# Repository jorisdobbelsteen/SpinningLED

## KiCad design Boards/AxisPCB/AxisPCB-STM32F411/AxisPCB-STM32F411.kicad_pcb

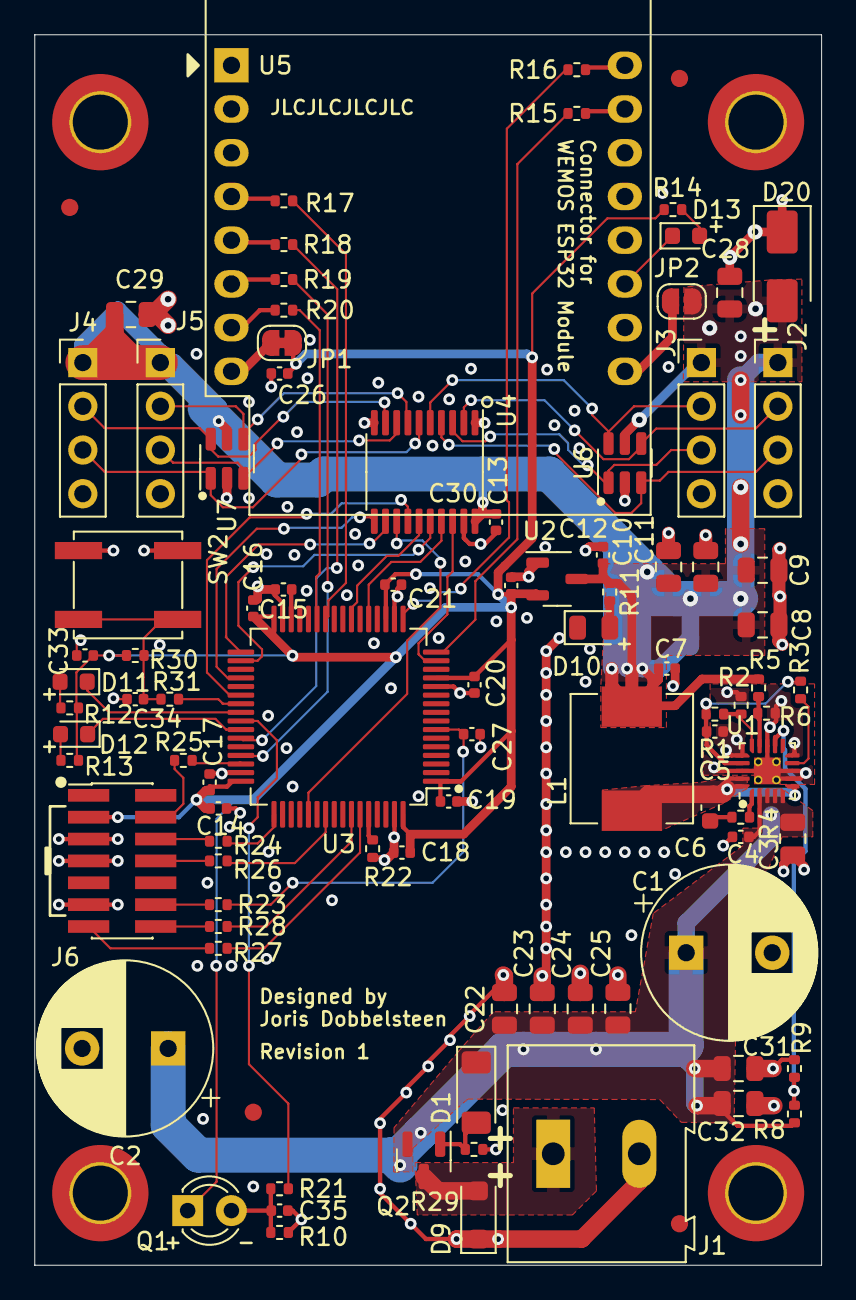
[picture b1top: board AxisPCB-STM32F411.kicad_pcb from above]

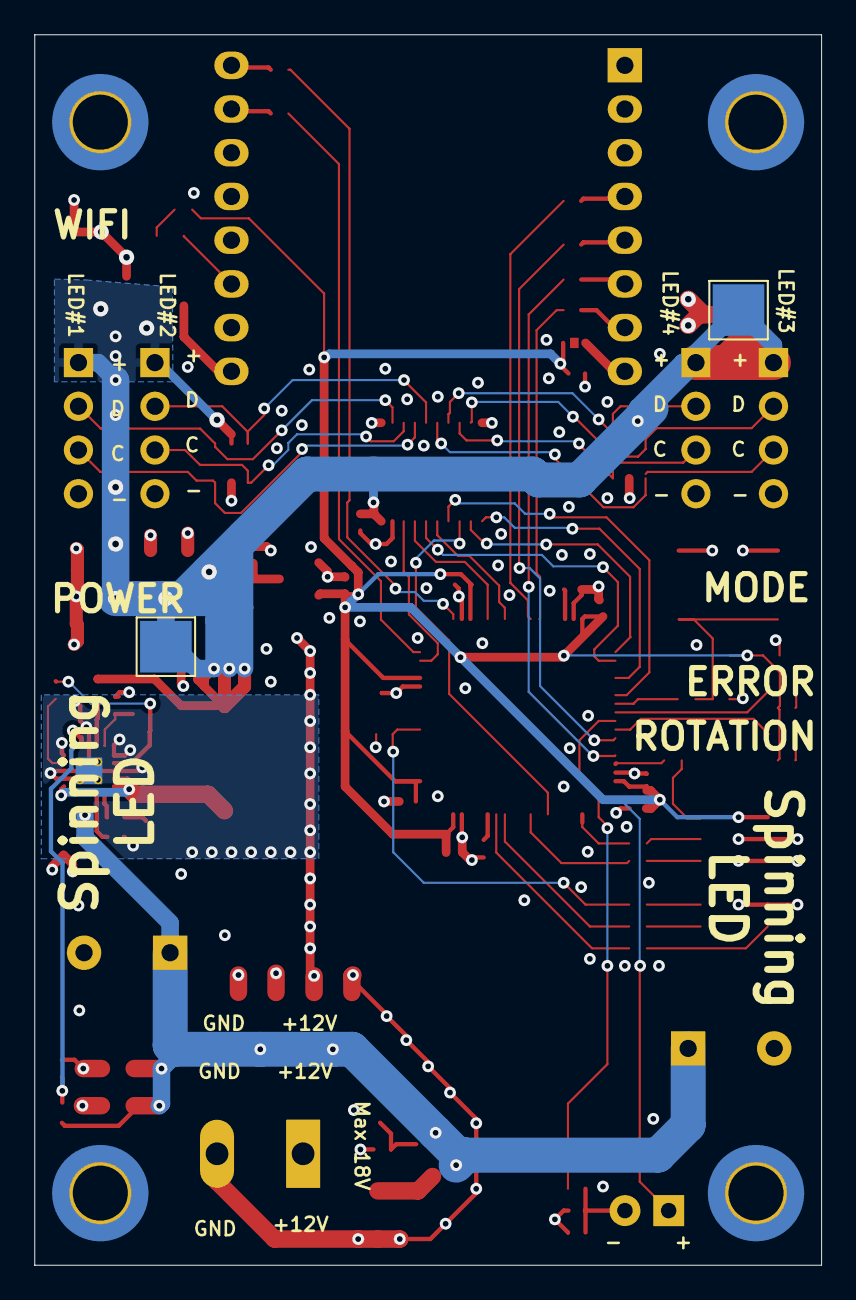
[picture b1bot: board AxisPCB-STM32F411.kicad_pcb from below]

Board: 4 copper layers, 45.7 x 71.5 mm, 101 parts (2 on the bottom side), 69 nets.

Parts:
C1, C2: 470u; CP_Radial_D10.0mm_P5.00mm
C3, C22, C23, C24, C25, C31, C32: 22u; C_0805_2012Metric
C4, C5, C12, C13, C33: 1u; C_0402_1005Metric
C6: 4u7; C_0603_1608Metric
C7, C16, C17, C18, C19, C20, C21, C27, C30, C34, C35: 0.1u; C_0402_1005Metric
C8, C9, C10, C11, C28, C29: 47u; C_0805_2012Metric
C14, C15, C26: 4.7u; C_0402_1005Metric
D1: ZMM5V6-M; D_MiniMELF
D9: SMF30CA; D_SOD-123F
D10: GREEN LED; LED_0805_2012Metric
D11: RED LED; LED_0603_1608Metric
D12: YELLOW LED; LED_0603_1608Metric
D13: BLUE LED; LED_0603_1608Metric
D20: SMAJ5.0A; D_SMA
FID1, FID2, FID3, FID4: Fiducial; Fiducial_1mm_Mask2mm
H1, H2, H3, H4: M3 Hole; MountingHole_3.2mm_M3_DIN965_Pad_TopBottom
J1: Conn_01x02_Pin; TerminalBlock_Altech_AK300-2_P5.00mm
J2, J3, J4, J5: Conn_01x04; PinHeader_1x04_P2.54mm_Vertical
J6: Conn_ST_STDC14; PinHeader_2x07_P1.27mm_Vertical_SMD
JP1: SolderJumper_2_Bridged; SolderJumper-2_P1.3mm_Bridged_RoundedPad1.0x1.5mm
JP2: SolderJumper_2_Open; SolderJumper-2_P1.3mm_Open_RoundedPad1.0x1.5mm
L1: 1.5u; L_Sunlord_MWSA0603S
Q1: INL-3APT30; LED_D3.0mm_Clear
Q2: AO3401A; SOT-23
R1: 330k 1%; R_0402_1005Metric
R2: 15k 1%; R_0402_1005Metric
R3: 100k; R_0402_1005Metric
R4: 0R; R_0402_1005Metric
R5: 200k 1%; R_0402_1005Metric
R6: 27k 1%; R_0402_1005Metric
R8: 200k; R_0402_1005Metric
R9: 51k; R_0402_1005Metric
R10, R29: 2K; R_0402_1005Metric
R11: 2.4k; R_0402_1005Metric
R12, R14, R31: 680R; R_0402_1005Metric
R13: 1.5k; R_0402_1005Metric
R15, R16, R17, R18, R19, R20, R23, R24, R25, R26: 22R; R_0402_1005Metric
R21, R27, R28: 100R; R_0402_1005Metric
R22, R30: 10k; R_0402_1005Metric
SW2: USER; SW_SPST_EVPBF
TP1, TP2: VCC; TestPoint_Pad_3.0x3.0mm
U1: TPS51396ARJER; VQFN-20-1EP_3x3mm_P0.45mm_EP1.55x1.55mm_ThermalVias
U2: XC6206P332MR; SOT-23-3
U3: STM32F411R_C-E_Tx; LQFP-64_10x10mm_P0.5mm
U4: 74AHCT245PW; TSSOP-20_4.4x6.5mm_P0.65mm
U5: WeMos_D1_mini; WEMOS_D1_mini_light
U6, U7: SRV05-4; SOT-23-6

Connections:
+3.3V: C13.1, C14.1, C16.2, C17.1, C18.1, C19.1, C20.1, C21.1, C26.1, C33.1, J6.3 (VCC), JP1.1 (A), Q1.1 (C), R12.1, R13.2, R14.2, R30.1, U2.2 (VO), U3.1 (VBAT), U3.13 (VDDA), U3.19 (VDD), U3.32 (VDD), U3.48 (VDD), U3.64 (VDD)
+5V: C7.1, C8.1, C9.1, C10.1, C11.1, C12.1, C28.1, C29.1, C30.1, D20.2 (A2), J2.1, J3.1, J4.1, J5.1, JP2.1 (A), L1.2, R5.1, R11.1, TP1.1, TP2.1, U2.3 (VI), U4.20 (VCC), U6.5 (VP), U7.5 (VP)
+12V: C1.1, C2.1, C3.1, C4.1, C22.1, C23.1, C24.1, C25.1, C31.1, C32.1, D1.1 (K), Q2.2 (S), R8.1, U1.2 (VIN), U1.3 (VIN_2), U1.4 (VIN_3), U1.5 (VIN_4)
/+12V_PIN: D9.2 (A2), J1.1, Q2.3 (D)
/SMPS 5V 8A/SW: C6.1, L1.1, U1.6 (SW), U1.19 (SW_2), U1.20 (SW_3)
/SMPS 5V 8A/VCC: C5.1, R1.1, R3.1, U1.17 (VCC)
BOOT0: R22.1, U3.60 (BOOT0)
ERROR_LED: D11.1 (K), U3.40 (PC9)
GND: C1.2, C2.2, C3.2, C4.2, C5.2, C7.2, C8.2, C9.2, C10.2, C11.2, C12.2, C13.2, C14.2, C15.2, C16.1, C17.2, C18.2, C19.2, C20.2, C21.2, C22.2, C23.2, C24.2, C25.2, C26.2, C27.2, C28.2, C29.2, C30.2, C31.2, C32.2, C33.2, C34.2, C35.1, D9.1 (A1), D10.1 (K), D20.1 (A1), H1.1, H2.1, H3.1, H4.1, J1.2, J2.4, J3.4, J4.4, J5.4, J6.5 (GND), J6.7 (GND), J6.11 (GNDDetect), R2.2, R6.2, R9.2, R10.2, R22.2, R29.2, SW2.1, U1.7 (GND), U1.8 (GND_2), U1.10 (NC_1), U1.13 (AGND), U1.16 (NC_2), U1.18 (GND_3), U1.21 (GND_4), U2.1 (GND), U3.12 (VSSA), U3.18 (VSS), U3.31 (VSS), U3.47 (VSS), U3.63 (VSS), U4.1 (A->B), U4.10 (GND), U4.19 (CE), U5.10 (GND), U6.2 (VN), U7.2 (VN)
LS1_C: J2.3, U4.4 (A2), U6.3 (IO2)
LS1_D: J2.2, U4.2 (A0), U6.4 (IO3)
LS2_C: J3.3, U4.3 (A1), U6.1 (IO1)
LS2_D: J3.2, U4.5 (A3), U6.6 (IO4)
LS3_C: J4.3, U4.6 (A4), U7.1 (IO1)
LS3_D: J4.2, U4.9 (A7), U7.6 (IO4)
LS4_C: J5.3, U4.8 (A6), U7.3 (IO2)
LS4_D: J5.2, U4.7 (A5), U7.4 (IO3)
NRST: C27.1, R23.1, U3.7 (NRST)
unnamed: C6.2, R4.2
unnamed: C34.1, R30.2, R31.2, SW2.2
unnamed: D1.2 (A), Q2.1 (G), R29.1
unnamed: D10.2 (A), R11.2
unnamed: D11.2 (A), R12.2
unnamed: D12.2 (A), R13.1
unnamed: D13.2 (A), R14.1
unnamed: J6.6 (JCLK/SWCLK), R24.2
unnamed: J6.8 (JTDO/SWO), R26.2
unnamed: J6.4 (JTMS/SWDIO), R25.2
unnamed: J6.13 (VCP_RX), R27.1
unnamed: J6.14 (VCP_TX), R28.1
unnamed: J6.12 (~RST), R23.2
unnamed: JP1.2 (B), U5.8 (3V3)
unnamed: JP2.2 (B), U5.9 (5V)
unnamed: C35.2, Q1.2 (E), R10.1, R21.1
unnamed: R4.1, U1.1 (BST)
unnamed: R5.2, R6.1, U1.14 (FB)
unnamed: R1.2, R2.1, U1.15 (MODE)
unnamed: R3.2, U1.9 (PGOOD)
unnamed: C15.1, U3.30 (VCAP1)
unnamed: R20.2, U5.7 (CS/D8)
unnamed: R18.2, U5.5 (MISO/D6)
unnamed: R19.2, U5.6 (MOSI/D7)
unnamed: R15.1, U5.15 (RX)
unnamed: R17.2, U5.4 (SCK/D5)
unnamed: R16.2, U5.16 (TX)
ROTATION_LED: D12.1 (K), U3.42 (PA9)
ROT_DETECT: R21.2, U3.41 (PA8)
SMPS_EN: R8.2, R9.1, U1.12 (EN)
SPI1_MOSI: U3.23 (PA7), U4.15 (B3)
SPI1_SCK: U3.21 (PA5), U4.17 (B1)
SPI2_MOSI: U3.36 (PB15), U4.11 (B7)
SPI2_SCK: U3.38 (PC7), U4.14 (B4)
SPI3_MOSI: U3.53 (PC12), U4.13 (B5)
SPI3_SCK: U3.33 (PB12), U4.12 (B6)
SPI4_MOSI: U3.15 (PA1), U4.18 (B0)
SPI4_SCK: U3.34 (PB13), U4.16 (B2)
SPI5_MISO: R19.1, U3.45 (PA12)
SPI5_MOSI: R18.1, U3.43 (PA10)
SPI5_NSS: R20.1, U3.27 (PB1)
SPI5_SCK: R17.1, U3.26 (PB0)
SWD_SWO: R26.1, U3.55 (PB3)
SWD_TCK: R24.1, U3.49 (PA14)
SWD_TMS: R25.1, U3.46 (PA13)
USART1_RX: R27.2, U3.59 (PB7)
USART1_TX: R28.2, U3.58 (PB6)
USART2_RX: R16.1, U3.17 (PA3)
USART2_TX: R15.2, U3.16 (PA2)
USER: R31.1, U3.39 (PC8)
WIFI_STAT_LED: D13.1 (K), U5.11 (D4)

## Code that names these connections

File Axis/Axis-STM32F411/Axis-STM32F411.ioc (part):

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Mcu.Name=STM32F411R(C-E)Tx
Mcu.Package=LQFP64
Mcu.UserName=STM32F411RETx
PA1.GPIOParameters=GPIO_Speed
PA1.GPIO_Speed=GPIO_SPEED_FREQ_HIGH
PA1.Mode=TX_Only_Simplex_Unidirect_Master
PA1.Signal=SPI4_MOSI
PA10.GPIOParameters=GPIO_Speed
PA10.GPIO_Speed=GPIO_SPEED_FREQ_HIGH
PA10.Mode=Full_Duplex_Slave
PA10.Signal=SPI5_MOSI
PA12.GPIOParameters=GPIO_Speed
PA12.GPIO_Speed=GPIO_SPEED_FREQ_HIGH
PA12.Mode=Full_Duplex_Slave
PA12.Signal=SPI5_MISO
PA13.GPIOParameters=GPIO_Label
PA13.GPIO_Label=TMS
PA13.Mode=Trace_Asynchronous_SW
PA13.Signal=SYS_JTMS-SWDIO
PA14.GPIOParameters=GPIO_Label
PA14.GPIO_Label=TCK
PA14.Mode=Trace_Asynchronous_SW
PA14.Signal=SYS_JTCK-SWCLK
PA2.GPIOParameters=GPIO_Speed,GPIO_Label
PA2.GPIO_Label=USART_TX
PA2.GPIO_Speed=GPIO_SPEED_FREQ_LOW
PA2.Mode=Asynchronous
PA2.Signal=USART2_TX
PA3.GPIOParameters=GPIO_Speed,GPIO_Label
PA3.GPIO_Label=USART_RX
PA3.GPIO_Speed=GPIO_SPEED_FREQ_LOW
PA3.Mode=Asynchronous
PA3.Signal=USART2_RX
PA5.GPIOParameters=GPIO_Speed
PA5.GPIO_Speed=GPIO_SPEED_FREQ_HIGH
PA5.Mode=TX_Only_Simplex_Unidirect_Master
PA5.Signal=SPI1_SCK
PA7.GPIOParameters=GPIO_Speed
PA7.GPIO_Speed=GPIO_SPEED_FREQ_HIGH
PA7.Mode=TX_Only_Simplex_Unidirect_Master
PA7.Signal=SPI1_MOSI
PA8.GPIOParameters=GPIO_Label
PA8.GPIO_Label=ROTATION_DETECT
PA8.Signal=S_TIM1_CH1
PA9.GPIOParameters=GPIO_ModeDefaultPP,GPIO_Label
PA9.GPIO_Label=ROTATION_LED
PA9.GPIO_ModeDefaultPP=GPIO_MODE_AF_OD
PA9.Signal=S_TIM1_CH2
PB0.GPIOParameters=GPIO_Speed
PB0.GPIO_Speed=GPIO_SPEED_FREQ_HIGH
PB0.Mode=Full_Duplex_Slave
PB0.Signal=SPI5_SCK
PB1.GPIOParameters=GPIO_Speed,GPIO_PuPd,GPIO_Label
PB1.GPIO_Label=SPI5_NSS
PB1.GPIO_PuPd=GPIO_PULLUP
PB1.GPIO_Speed=GPIO_SPEED_FREQ_HIGH
PB1.Signal=SharedStack_PB1
PB1.Stacked=true
PB12.GPIOParameters=GPIO_Speed
PB12.GPIO_Speed=GPIO_SPEED_FREQ_HIGH
PB12.Mode=TX_Only_Simplex_Unidirect_Master
PB12.Signal=SPI3_SCK
PB13.GPIOParameters=GPIO_Speed
PB13.GPIO_Speed=GPIO_SPEED_FREQ_HIGH
PB13.Mode=TX_Only_Simplex_Unidirect_Master
PB13.Signal=SPI4_SCK
PB15.GPIOParameters=GPIO_Speed
PB15.GPIO_Speed=GPIO_SPEED_FREQ_HIGH
PB15.Mode=TX_Only_Simplex_Unidirect_Master
PB15.Signal=SPI2_MOSI
PB3.GPIOParameters=GPIO_Label
PB3.GPIO_Label=SWO
PB3.Mode=Trace_Asynchronous_SW
PB3.Signal=SYS_JTDO-SWO
PC12.GPIOParameters=GPIO_Speed
PC12.GPIO_Speed=GPIO_SPEED_FREQ_HIGH
PC12.Mode=TX_Only_Simplex_Unidirect_Master
PC12.Signal=SPI3_MOSI
PC7.GPIOParameters=GPIO_Speed
PC7.GPIO_Speed=GPIO_SPEED_FREQ_HIGH
PC7.Mode=TX_Only_Simplex_Unidirect_Master
PC7.Signal=SPI2_SCK
PC8.GPIOParameters=GPIO_Label,GPIO_ModeDefaultEXTI
PC8.GPIO_Label=MODE_BUTTON
PC8.GPIO_ModeDefaultEXTI=GPIO_MODE_IT_FALLING
PC8.Signal=GPXTI8
PC9.GPIOParameters=GPIO_ModeDefaultPP,GPIO_Label
PC9.GPIO_Label=ERROR_LED [TIM3_CH4]
PC9.GPIO_ModeDefaultPP=GPIO_MODE_AF_OD
PC9.Signal=S_TIM3_CH4
PH0\ -\ OSC_IN.Signal=RCC_OSC_IN
PH1\ -\ OSC_OUT.Signal=RCC_OSC_OUT
RCC.HSE_VALUE=8000000
RCC.SYSCLKFreq_VALUE=64000000
RCC.SYSCLKSource=RCC_SYSCLKSOURCE_PLLCLK
board=NUCLEO-F411RE
boardIOC=true

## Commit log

2023-06-07 Initial commit * PCB for Axis board, revision 1 * Documentation for design ready * Project setup for axis. No code and pinout not yet aligned with PCB
2023-08-09 Axis PCB Errata document added Minor documentation update
2023-08-09 Board bring-up with 2 LED strings
    Drive 2 LED strings of 52 leds with changing hue
    Error LED and rotation LED
    CPU at 80 MHz and SPI busses run at 20 Mbps
    Most peripherals are now configured via STM32CubeMX
    Testing of rotation sensor not performed, as device is not yet onboard
    Testing of SPI5 for ESP32 not done, as ESP32 not installed
2023-08-10 Enable all compiler warnings (GCC) and fix code
2023-08-11 Switch to Low Level drivers rather than HAL
2023-08-11 Drive SPI busses using pixel timer (TIM2) interrupt Main loop can put CPU into sleep mode Interrupts now have preemption so pixel timer will fire reliably
2023-08-12 SPI DMA streams access SRAM with words instead of bytes (using FIFO)
2023-10-21 Control box with PWM signal to separate BLDC controller based on ST Nucleo-F303 development board
    Peripherals and full concept of control loop implemented.
    Actual control is not implemented.
2023-10-22 Working speed controller (keeps speed at +/- 0.2 rpm without swinging bars)
2023-10-23 Improve tuning of speed controller PID coefficients to run at 15 rpm
2023-10-25 Axis board: STM32CubeMX 6.9.0 upgrade. Higher LED brightness.
2023-10-31 Better tuning of PID with heavier arms
2023-11-01 Axis board: rotation detect, color scheme, reduced SPI speed
    Rotation detection sensor support.
    Color with Hue & RGB (algorithms).
    Reduce SPI speed to 16 Mbps (processor to 64 MHz).
2023-11-02 Axis board: double buffer SPI and slow update on no rotation
2023-11-02 Axis board: add color patterns and enable mode button
2023-11-02 Axis board: add two-channel and four-channel build config. Fix compile issues with two-channel mode. Update .gitignore.
2023-11-07 Axis board: actually working and with cat image Fix mistakes with x & y coordinates and limits. Added cat image (includes generator from image to c code).
2024-02-07 Communication via SPI5 to external app
    Enable SPI5 as slave to receive commands. Provides current state (working). Supports setting a program (untested).
    Tune optimization and enable LTO for release build
2024-02-07 Images with converter script
    Allow images to be added to the Axis board build
2024-02-07 Allow Android to Axis MCU communication via ESP32-C3
    Adds platform.io project for this MCU
2024-02-07 Update documentation and design description
